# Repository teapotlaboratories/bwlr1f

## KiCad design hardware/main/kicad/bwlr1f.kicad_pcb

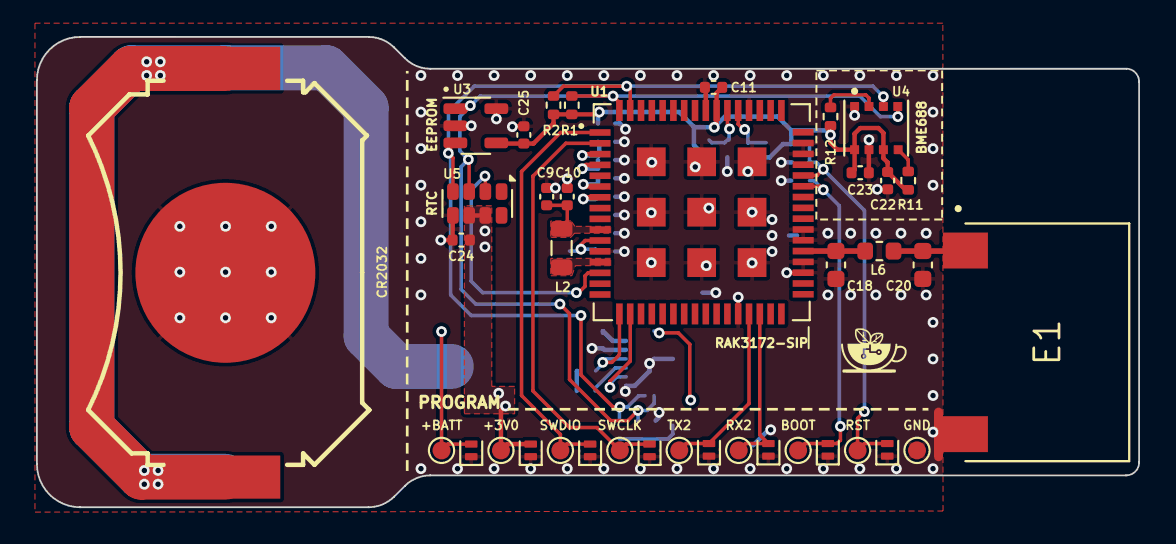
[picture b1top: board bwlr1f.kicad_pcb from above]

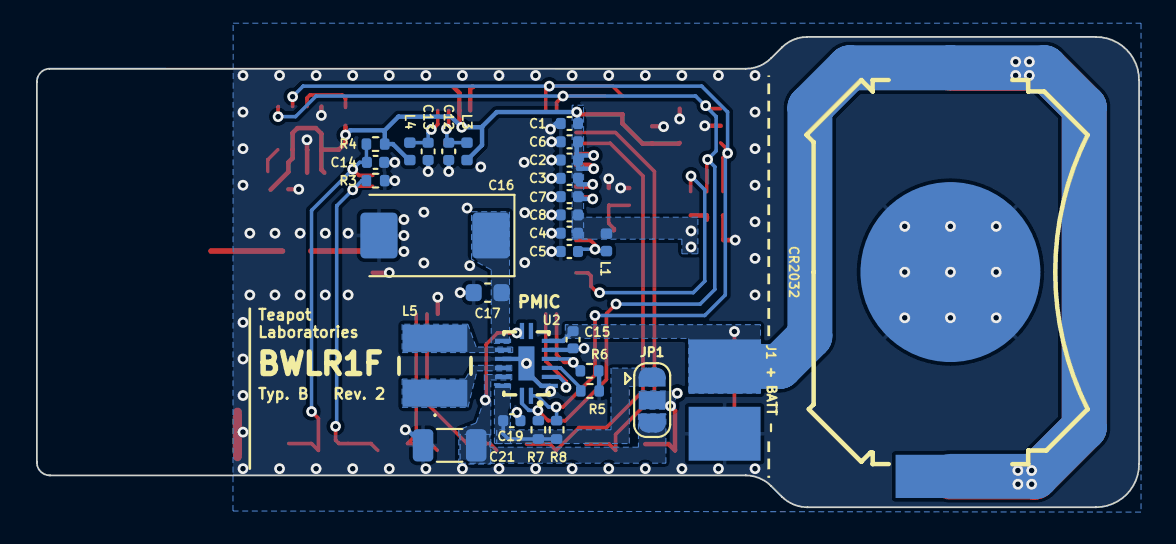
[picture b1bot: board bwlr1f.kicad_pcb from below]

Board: 4 copper layers, 61.2 x 26.1 mm, 68 parts (30 on the bottom side), 29 nets.

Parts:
BT1, BT2: Battery_Cell; BAT-SMD_MY-2032-12
C1, C3, C4: 4u7; C_0402_1005Metric
C2, C12, C13, C15, C19, C25: 1u; C_0402_1005Metric
C5, C6, C7, C8, C10, C11, C14, C22, C23, C24: 100n; C_0402_1005Metric
C9: 470n; C_0402_1005Metric
C16: 470u; CP_EIA-7343-40_Kemet-Y
C17: 10u; C_0603_1608Metric
C18, C20: DNP; C_0603_1608Metric
C21: 22u; C_1206_3216Metric
D1, D2, D3, D4, D5, D6, D7, D8: ESD5651N; D_SOD-882
E1: ANT-915-USP410; XDCR_ANT-915-USP410
J1: Conn_01x02; Battery_Pad
JP1: OUTPUT_SELECT; SolderJumper-3_P1.3mm_Open_RoundedPad1.0x1.5mm
L1, L3, L4: 120; L_0402_1005Metric
L2: 15u; L_0805_2012Metric
L5: 15u; 74404042150
L6: 0; L_0603_1608Metric
R1, R2: 4K7; R_0402_1005Metric
R3, R4, R11, R12: 10K; R_0402_1005Metric
R5, R6: 100K; R_0402_1005Metric
R7, R8: 1K; R_0402_1005Metric
TP1, TP2, TP3, TP4, TP5, TP6, TP7, TP8, TP9: ProgPin; TestPoint_Pad_D1.0mm
U1: RAK3172-SIP; RAK3172-SiP_LGA75
U2: NBM7100ABQX
U3: ZD24C08A; SOT-23-5
U4: BME688; BME680-PSON80P300X300X100-8N
U5: RV-3028-C7; MicroCrystal_C7_SON-8_1.5x3.2mm_P0.9mm

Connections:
+3V0: C1.2, C2.2, C3.2, C4.2, C6.2, C7.2, C8.2, C11.2, C22.2, C23.2, C24.2, C25.2, D8.2 (A2), JP1.2 (C), L1.1, L3.2, L4.2, R1.1, R2.1, R4.1, R11.1, R12.1, TP1.1, U1.3 (VDD), U1.4 (VBAT), U1.6 (VREF+), U1.7 (VDDA), U1.55 (VDD), U3.4 (VCC), U4.6 (VDDIO), U4.8 (VDD), U5.6 (VBACKUP), U5.7 (VDD)
/+VDP: C19.2, JP1.1 (A), R7.1, R8.1, U2.15 (VDP)
/ANT: C20.2, E1.1, L6.2
/BATT+: BT1.1 (+), BT2.1 (+), C15.2, D7.2 (A2), J1.1, TP2.1, U2.7 (VBT)
/BOOT: D1.2 (A2), R3.1, TP8.1, U1.43 (BOOT_0)
/RDY: U1.18 (PB7/UART1_RX), U2.3 (RDY)
/RF: C18.2, L6.1, U1.37 (RF_OUT)
/RST: C14.2, D2.2 (A2), R4.2, TP7.1, U1.44 (NRST)
/RTC_WKUP: U1.14 (PB3), U5.2 (~INT)
/RX2: D6.2 (A2), TP3.1, U1.30 (PA3/UART2_RX)
/SCL: R1.2, R7.2, U1.64 (PA12/I2C2_SCL), U2.16 (SCL), U3.1 (SCL), U4.4 (SCK), U5.3 (SCL)
/SDA: R2.2, R8.2, U1.63 (PA11/I2C2_SDA), U2.1 (SDA), U3.3 (SDA), U4.3 (SDI), U5.4 (SDA)
/START: R6.1, U1.17 (PB6/UART1_TX), U2.5 (START)
/SWCLK: D4.2 (A2), TP5.1, U1.2 (PA14/SWCLK)
/SWDIO: D3.2 (A2), TP6.1, U1.1 (PA13/SWDIO)
/TX2: D5.2 (A2), TP4.1, U1.29 (PA2/UART2_TX)
GND: BT1.2 (-), BT2.2 (-), C1.1, C2.1, C3.1, C4.1, C5.1, C6.1, C7.1, C8.1, C9.1, C10.1, C11.1, C12.1, C13.1, C14.1, C15.1, C16.2, C17.1, C18.1, C19.1, C20.1, C21.1, C22.1, C23.1, C24.1, C25.1, D1.1 (A1), D2.1 (A1), D3.1 (A1), D4.1 (A1), D5.1 (A1), D6.1 (A1), D7.1 (A1), D8.1 (A1), E1.2, J1.2, R3.2, R5.2, R6.2, TP9.1, U1.12 (GND), U1.28 (GND), U1.35 (GND), U1.36 (GND), U1.38 (GND), U1.39 (GND), U1.46 (GND), U1.47 (GND), U1.52 (GND), U1.56 (GND), U1.65 (GND), U1.66 (GND), U1.67 (GND), U1.68 (GND), U1.69 (GND), U1.70 (GND), U1.71 (GND), U1.72 (GND), U1.73 (GND), U2.2 (TST), U2.6 (VSS_1), U2.12 (VSSP), U2.17 (VSS_2), U3.2 (VSS), U3.5 (WP), U4.1 (GND), U4.7 (GND), U5.5 (VSS)
unnamed: C21.2, JP1.3 (B), U2.9 (VDHS), U2.14 (VDH)
unnamed: C5.2, L1.2, U1.11 (VDDMPS)
unnamed: C13.2, L4.1, U1.53 (VDDPA)
unnamed: C12.2, L3.1, U1.54 (VDDRF)
unnamed: C9.2, C10.2, L2.1, U1.10 (VFBSMPS)
unnamed: L2.2, U1.13 (VLXSMPS)
unnamed: R5.1, U2.4 (ADR)
unnamed: C16.1, C17.2, U2.10 (CAP)
unnamed: L5.1, U2.13 (LX1)
unnamed: L5.2, U2.11 (LX2)
unnamed: R12.2, U4.2 (CSB)
unnamed: R11.2, U4.5 (SDO)

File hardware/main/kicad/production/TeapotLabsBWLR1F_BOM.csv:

Id,Designator,Quantity,Manufacturer,Manufacturer Part Number,Value,Description,Footprint,Type,Distributor,Distributor Part Number,Distributor Link,Datasheet
1,"BT1,BT2",2,MYOUNG,MY-2032-12,Battery_Cell,Battery clip Nickel -25?~+85? Phosphor Bronze CR2032 SMD Button And Strip Battery Connector ROHS,bwlr1f:BAT-SMD_MY-2032-12,SMT,LCSC,C964833,https://www.lcsc.com/product-detail/Battery-Connectors_MYOUN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,https://datasheet.lcsc.com/lcsc/2012181809_MYOUNG-MY-2032-12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
2,"C1,C3,C4",3,Samsung Electro-Mechanics,CL05A475KP5NRNC,4u7,10V 4.7uF X5R ñ10% 0402 Multilayer Ceramic Capacitors MLCC - SMD/SMT ROHS,Capacitor_SMD:C_0402_1005Metric,SMT,LCSC,C368809,https://www.lcsc.com/product-detail/Multilayer-Ceramic-Capac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,https://datasheet.lcsc.com/lcsc/2304140030_Samsung-Electro-M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
3,"C2,C12,C13,C15,C19,C25",6,Samsung Electro-Mechanics,CL05A105KO5NNNC,1u,16V 1uF X5R ñ10% 0402 Multilayer Ceramic Capacitors MLCC - SMD/SMT ROHS ,Capacitor_SMD:C_0402_1005Metric,SMT,LCSC,C29266,https://www.lcsc.com/product-detail/Multilayer-Ceramic-Capac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,https://datasheet.lcsc.com/lcsc/2304140030_Samsung-Electro-M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
4,"C5,C6,C7,C8,C10,C11,C14,C22,C23,C24",10,Samsung Electro-Mechanics,CL05B104KO5NNNC,100n,16V 100nF X7R ñ10% 0402 Multilayer Ceramic Capacitors MLCC - SMD/SMT ROHS,Capacitor_SMD:C_0402_1005Metric,SMT,LCSC,C1525,https://www.lcsc.com/product-detail/Multilayer-Ceramic-Capac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,https://datasheet.lcsc.com/lcsc/2304140030_Samsung-Electro-M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
5,C9,1,Samsung Electro-Mechanics,CL05A474KP5NNNC,470n,10V 470nF X5R ñ10% 0402 Multilayer Ceramic Capacitors MLCC - SMD/SMT ROHS,Capacitor_SMD:C_0402_1005Metric,SMT,LCSC,C47339,https://www.lcsc.com/product-detail/Multilayer-Ceramic-Capac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,https://datasheet.lcsc.com/lcsc/2304140030_Samsung-Electro-M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
6,C16,1,KYOCERA AVX,TCJ5477M016R0100E,470u,Cap Tant Poly 470uF 16V 2917,Capacitor_Tantalum_SMD:CP_EIA-7343-40_Kemet-Y,SMT,Digikey,478-13191-1-ND,https://www.digikey.com/en/products/detail/kyocera-avx/TCJ54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,https://datasheets.kyocera-avx.com/TCJ.pdf
7,C17,1,Samsung Electro-Mechanics,CL10A106KO8NQNC,10u,16V 10uF X5R ñ10% 0603 Multilayer Ceramic Capacitors MLCC - SMD/SMT ROHS,Capacitor_SMD:C_0603_1608Metric,SMT,LCSC,C962136,https://www.lcsc.com/product-detail/Multilayer-Ceramic-Capac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,https://datasheet.lcsc.com/lcsc/2304140030_Samsung-Electro-M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
8,"C18,C20",2,-,-,DNP,DNP,Capacitor_SMD:C_0603_1608Metric,SMT,-,-,-,-
9,C21,1,Chinocera,HGC1206R7226K160NSPJ,22u,16V 22uF X7R ñ10% 1206 Multilayer Ceramic Capacitors MLCC - SMD/SMT ROHS,Capacitor_SMD:C_1206_3216Metric,SMT,LCSC,C7472972,https://www.lcsc.com/product-detail/Multilayer-Ceramic-Capac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,https://datasheet.lcsc.com/lcsc/2308041038_Chinocera-HGC1206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
10,"D1,D2,D3,D4,D5,D6,D7,D8",8,WILLSEMI(Will Semicon),ESD5651N-2/TR,ESD5651N,35A@8/20us 15V 4.5V DFN1006-2L Electrostatic and Surge Protection (TVS/ESD) ROHS,Diode_SMD:D_SOD-882,SMT,LCSC,C239784,https://www.lcsc.com/product-detail/Electrostatic-and-Surge-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,https://www.lcsc.com/datasheet/lcsc_datasheet_1808311544_WIL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
11,"L1,L3,L4",3,Murata Electronics,BLM15PD121SN1D,120,90mê ñ25% 120ê@100MHz 0402 Ferrite Beads ROHS,Inductor_SMD:L_0402_1005Metric,SMT,LCSC,C76891,https://www.lcsc.com/product-detail/Ferrite-Beads_Murata-Ele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,https://datasheet.lcsc.com/lcsc/2304140030_Murata-Electronic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
12,L2,1,TDK,MLZ2012M150WT000,15u,15uH ñ20% 120mA 950mê 0805 Inductors (SMD) ROHS,Inductor_SMD:L_0805_2012Metric,SMT,LCSC,C383402,https://www.lcsc.com/product-detail/Inductors-SMD_TDK-MLZ201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,https://datasheet.lcsc.com/lcsc/2304140030_TDK-MLZ2012M150WT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
13,L5,1,Wurth Elektronik,74404042150,15u,Fixed Ind 15uH 850mA 210 mOhm SMD,bwlr1f:74404042150,SMT,Digikey,732-5509-1-ND,https://www.digikey.com/en/products/detail/w%C3%BCrth-elektr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,https://www.we-online.com/katalog/datasheet/74404042150.pdf
14,L6,1,UNI-ROYAL(Uniroyal Elec),0603WAF0000T5E,0,100mW Thick Film Resistors 75V ñ1% 0ê 0603 Chip Resistor - Surface Mount ROHS ,Inductor_SMD:L_0603_1608Metric,SMT,LCSC,C21189,https://www.lcsc.com/product-detail/Chip-Resistor-Surface-Mo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,https://datasheet.lcsc.com/lcsc/2206010130_UNI-ROYAL-Uniroya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
15,"R1,R2",2,YAGEO,RC0402FR-074K7L,4K7,62.5mW Thick Film Resistors 50V ñ100ppm/? ñ1% 4.7kê 0402 Chip Resistor - Surface Mount ROHS,Resistor_SMD:R_0402_1005Metric,SMT,LCSC,C105871,https://www.lcsc.com/product-detail/Chip-Resistor-Surface-Mo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,https://datasheet.lcsc.com/lcsc/2304140030_YAGEO-RC0402FR-07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
16,"R3,R4,R11,R12",4,YAGEO,RC0402FR-0710KL,10K,62.5mW Thick Film Resistors 50V ñ100ppm/? ñ1% 10kê 0402 Chip Resistor - Surface Mount ROHS,Resistor_SMD:R_0402_1005Metric,SMT,LCSC,C60490,https://www.lcsc.com/product-detail/Chip-Resistor-Surface-Mo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,https://datasheet.lcsc.com/lcsc/2304140030_YAGEO-RC0402FR-07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
17,"R5,R6",2,YAGEO,RC0402FR-07100KL,100K,62.5mW Thick Film Resistors 50V ñ100ppm/? ñ1% 100kê 0402 Chip Resistor - Surface Mount ROHS ,Resistor_SMD:R_0402_1005Metric,SMT,LCSC,C60491,https://www.lcsc.com/product-detail/Chip-Resistor-Surface-Mo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,https://datasheet.lcsc.com/lcsc/2304140030_YAGEO-RC0402FR-07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
18,"R7,R8",2,YAGEO,RC0402FR-071KL,1K,62.5mW Thick Film Resistors 50V ñ100ppm/? ñ1% 1kê 0402 Chip Resistor - Surface Mount ROHS,Resistor_SMD:R_0402_1005Metric,SMT,LCSC,C106235,https://www.lcsc.com/product-detail/Chip-Resistor-Surface-Mo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,https://datasheet.lcsc.com/lcsc/2304140030_YAGEO-RC0402FR-07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
19,U1,1,RAKwireless,306039,RAK3172-SIP,RAK3172-SIP,bwlr1f:RAK3172-SiP_LGA75,SMT,RAKwireless,306039,Contact inquiry@rakwireless.com for SKU: 306039,https://docs.rakwireless.com/Product-Categories/WisDuo/RAK31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
20,U2,1,Nexperia,NBM7100ABQX,NBM7100ABQX,Coin Cell Battery Life Booster,bwlr1f:NBM7100ABQX,SMT,Digikey,1727-NBM7100ABQXCT-ND,https://www.digikey.com/en/products/detail/nexperia-usa-inc/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,https://assets.nexperia.com/documents/data-sheet/NBM7100.pdf
21,U3,1,Zetta,ZD24C08A-STGMT,ZD24C08A,8Kbit 1MHz I2C SOT-23-5 EEPROM ROHS,Package_TO_SOT_SMD:SOT-23-5,SMT,LCSC,C2896640,https://www.lcsc.com/product-detail/EEPROM_Zetta-ZD24C08A-ST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,https://datasheet.lcsc.com/lcsc/2109141830_Zetta-ZD24C08A-ST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
22,U4,1,Bosch Sensortec,BME688,BME688,Sensor Gas/Hum/Pres/Temp I2C SPI,bwlr1f:BME680-PSON80P300X300X100-8N,SMT,Digikey,828-BME688CT-ND,https://www.digikey.com/en/products/detail/bosch-sensortec/B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,https://www.bosch-sensortec.com/media/boschsensortec/downloa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
23,U5,1,Micro Crystal,RV-3028-C7 32.768kHz 1ppm TA QC ,RV-3028-C7,"Realtime Clock/Calendar I2C Interface, Extreme Low Power, 1.1 V to 5.5 V, MicroCrystal C7",Package_SON:MicroCrystal_C7_SON-8_1.5x3.2mm_P0.9mm,SMT,LCSC,C3019759,https://www.lcsc.com/product-detail/Real-Time-Clocks_Micro-C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,https://www.lcsc.com/datasheet/lcsc_datasheet_2302171010_Mic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

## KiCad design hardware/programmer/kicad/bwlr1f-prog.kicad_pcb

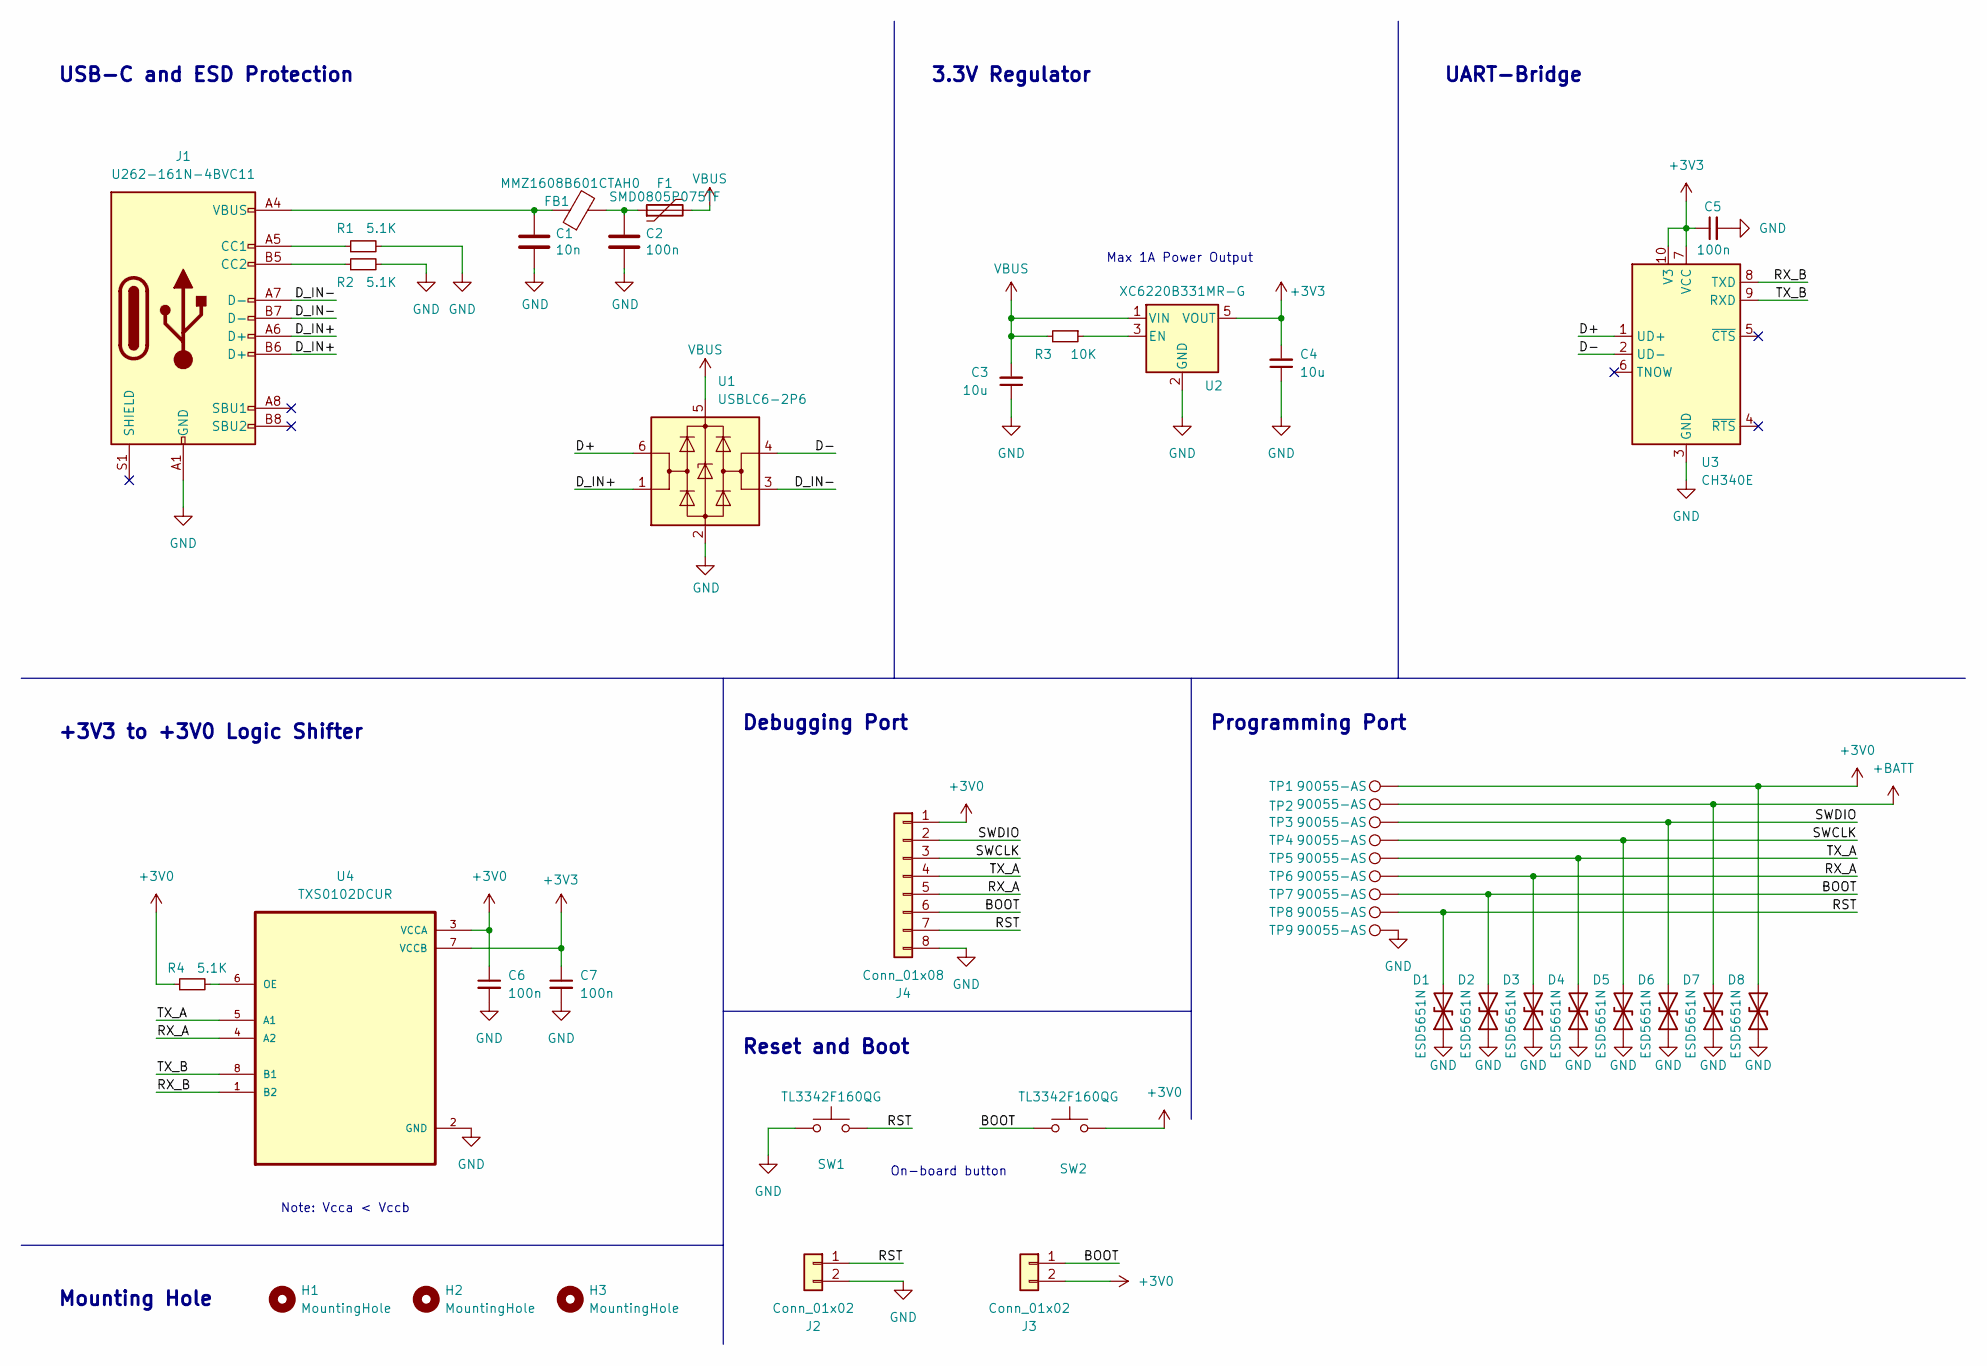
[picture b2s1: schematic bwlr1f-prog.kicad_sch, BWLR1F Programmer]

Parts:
C1: 10n; C_0402_1005Metric; Part Number CC0402KRX7R9BB103
C2: 100n; C_0402_1005Metric; Part Number CC0402KRX5R6BB104
C3, C4: 10u; C_0805_2012Metric; Part Description Ceramic Capacitor 10uF 10% 10V X5R
C5: 100n; C_0603_1608Metric; Part Description Ceramic Capacitor 100nF 10% 10V X7R
C6, C7: 100n; C_0402_1005Metric; Manufacturer Part Number CL05B104KO5NNNC
D1, D2, D3, D4, D5, D6, D7, D8: ESD5651N; D_SOD-882; Manufacturer Part Number ESD5651N-2/TR
F1: SMD0805P075TF; Fuse_0805_2012Metric; Part Number SMD0805P075TF
FB1: MMZ1608B601CTAH0; L_0603_1608Metric; Part Number MMZ1608B601CTAH0
H1, H2, H3: MountingHole; MountingHole_2.2mm_M2_DIN965_Pad
J1: U262-161N-4BVC11; USB_C_Receptacle_XKB_U262-16XN-4BVC11; Part Number U262-161N-4BVC11
J2, J3: Conn_01x02; PinHeader_1x02_P2.54mm_Horizontal
J4: Conn_01x08; PinHeader_1x08_P2.54mm_Horizontal
R1, R2, R4: 5.1K; R_0402_1005Metric; Part Description Resistor 5.1K 1% 62.5mW
R3: 10K; R_0603_1608Metric; Part Description Resistor 10k 5% 100mW
SW1, SW2: TL3342F160QG; SW_SPST_TL3342; Part Number TL3342F160QG
TP1, TP2, TP3, TP4, TP5, TP6, TP7, TP8, TP9: 90055-AS; Manufacturer Part Number 90055-AS
U1: USBLC6-2P6; SOT-666; Part Number USBLC6-2P6
U2: XC6220B331MR-G; SOT-23-5; Part Number XC6220B331MR-G
U3: CH340E; MSOP-10_3x3mm_P0.5mm; Part Number CH340E
U4: TXS0102DCUR; SOP50P310X90-8N; Manufacturer Part Number TXS0102DCUR

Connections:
+3V0: C6.1, D8.2 (A2), J3.2, J4.1, R4.1, SW2.2, TP1.1, U4.3 (VCCA)
+3V3: C4.2, C5.1, C7.1, U2.5 (VOUT), U3.7 (VCC), U3.10 (V3), U4.7 (VCCB)
+BATT: D7.2 (A2), TP2.1
/BOOT: D2.2 (A2), J3.1, J4.6, SW2.1, TP7.1
/D+: U1.6 (I/O1), U3.1 (UD+)
/D-: U1.4 (I/O2), U3.2 (UD-)
/D_IN+: J1.A6 (D+), J1.B6 (D+), U1.1 (I/O1)
/D_IN-: J1.A7 (D-), J1.B7 (D-), U1.3 (I/O2)
/RST: D1.2 (A2), J2.1, J4.7, SW1.2, TP8.1
/RX_A: D3.2 (A2), J4.5, TP6.1, U4.4 (A2)
/RX_B: U3.8 (TXD), U4.1 (B2)
/SWCLK: D5.2 (A2), J4.3, TP4.1
/SWDIO: D6.2 (A2), J4.2, TP3.1
/TX_A: D4.2 (A2), J4.4, TP5.1, U4.5 (A1)
/TX_B: U3.9 (RXD), U4.8 (B1)
GND: C1.2, C2.2, C3.1, C4.1, C5.2, C6.2, C7.2, D1.1 (A1), D2.1 (A1), D3.1 (A1), D4.1 (A1), D5.1 (A1), D6.1 (A1), D7.1 (A1), D8.1 (A1), J1.A1 (GND), J1.A12 (GND), J1.B1 (GND), J1.B12 (GND), J2.2, J4.8, R1.2, R2.2, SW1.1, TP9.1, U1.2 (GND), U2.2 (GND), U3.3 (GND), U4.2 (GND)
unnamed: C1.1, FB1.1, J1.A4 (VBUS), J1.A9 (VBUS), J1.B4 (VBUS), J1.B9 (VBUS)
unnamed: C2.1, F1.1, FB1.2
unnamed: J1.A5 (CC1), R1.1
unnamed: J1.B5 (CC2), R2.1
unnamed: R3.1, U2.3 (EN)
unnamed: R4.2, U4.6 (OE)
VBUS: C3.2, F1.2, R3.2, U1.5 (VBUS), U2.1 (VIN)

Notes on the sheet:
Debugging Port
Mounting Hole
UART-Bridge
Max 1A Power Output
Note: Vcca < Vccb
Programming Port
USB-C and ESD Protection
On-board button
Reset and Boot
+3V3 to +3V0 Logic Shifter
3.3V Regulator

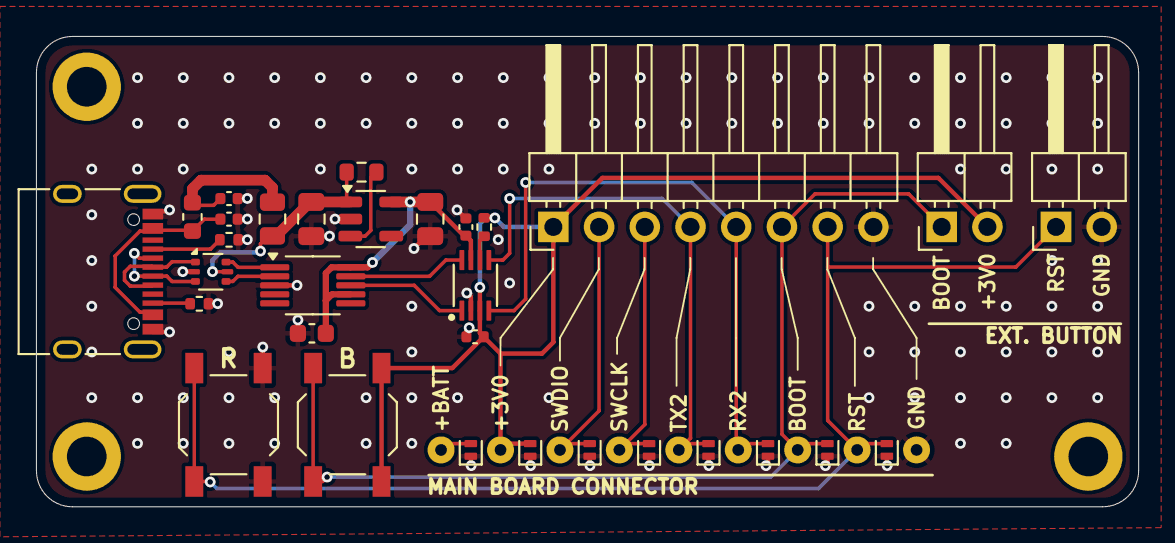
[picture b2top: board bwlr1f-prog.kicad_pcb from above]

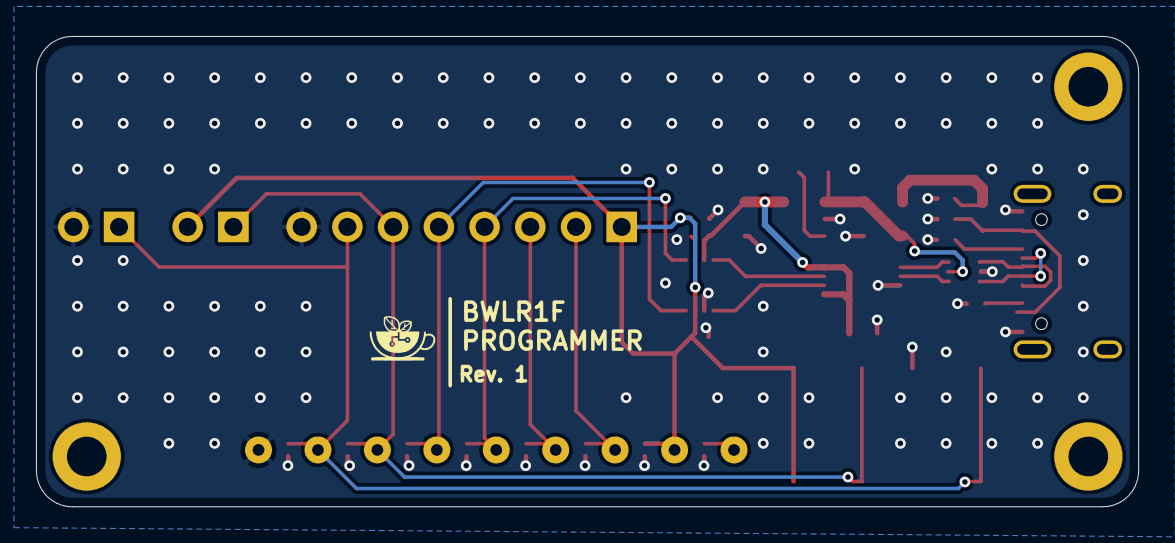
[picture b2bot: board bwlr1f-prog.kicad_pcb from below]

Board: 2 copper layers, 61.2 x 26.1 mm, 43 parts (9 on the bottom side), 23 nets.

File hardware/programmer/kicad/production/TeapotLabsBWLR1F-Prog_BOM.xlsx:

Id | Designator | Quantity | Manufacturer | Manufacturer Part Number | Value | Description | Footprint | Type | Distributor | Distributor Part Number | Distributor Link | Datasheet
1 | C1 | 1 | YAGEO | CC0402KRX7R9BB103 | 10n | 50V 10nF X7R ±10% 0402 Multilayer Ceramic Capacitors MLCC - SMD/SMT ROHS | Capacitor_SMD:C_0402_1005Metric | SMT | LCSC | C60133 | https://www.lcsc.com/product-detail/Multilayer-Ceramic-Capac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 | https://www.lcsc.com/datasheet/lcsc_datasheet_2304140030_YAG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
2 | C2,C6,C7 | 3 | Samsung Electro-Mechanics | CL05B104KO5NNNC | 100n | 16V 100nF X7R ±10% 0402 Multilayer Ceramic Capacitors MLCC - SMD/SMT ROHS | Capacitor_SMD:C_0402_1005Metric | SMT | LCSC | C1525 | https://www.lcsc.com/product-detail/Multilayer-Ceramic-Capac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 | https://www.lcsc.com/datasheet/lcsc_datasheet_2304140030_Sam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
3 | C3,C4 | 2 | Samsung Electro-Mechanics | CL21A106KPFNNNE | 10u | 10V 10uF X5R ±10% 0805 Multilayer Ceramic Capacitors MLCC - SMD/SMT ROHS | Capacitor_SMD:C_0805_2012Metric | SMT | LCSC | C17024 | https://www.lcsc.com/product-detail/Multilayer-Ceramic-Capac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 | https://www.lcsc.com/datasheet/lcsc_datasheet_2304140030_Sam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
4 | C5 | 1 | Samsung Electro-Mechanics | CL10B104KB8NNNC | 100n | 50V 100nF X7R ±10% 0603 Multilayer Ceramic Capacitors MLCC - SMD/SMT ROHS | Capacitor_SMD:C_0603_1608Metric | SMT | LCSC | C1591 | https://www.lcsc.com/product-detail/Multilayer-Ceramic-Capac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 | https://www.lcsc.com/datasheet/lcsc_datasheet_2304140030_Sam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
5 | D1,D2,D3,D4,D5,D6,D7,D8 | 8 | WILLSEMI(Will Semicon) | ESD5651N-2/TR | ESD5651N | 35A@8/20us 15V 4.5V DFN1006-2L Electrostatic and Surge Protection (TVS/ESD) ROHS | Diode_SMD:D_SOD-882 | SMT | LCSC | C239784 | https://www.lcsc.com/product-detail/Electrostatic-and-Surge-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 | https://www.lcsc.com/datasheet/lcsc_datasheet_1808311544_WIL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
6 | F1 | 1 | RUILON(Shenzhen Ruilongyuan Elec) | SMD0805P075TF | SMD0805P075TF | 6V 750mA 40A 1.5A 0805 Resettable Fuses ROHS | Fuse:Fuse_0805_2012Metric | SMT | LCSC | C20979 | https://www.lcsc.com/product-detail/Resettable-Fuses_RUILON-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 | https://www.lcsc.com/datasheet/lcsc_datasheet_2403081022_RUI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
7 | FB1 | 1 | TDK | MMZ1608B601CTAH0 | MMZ1608B601CTAH0 | 400m? ±25% 600?@100MHz 0603 Ferrite Beads ROHS | Inductor_SMD:L_0603_1608Metric | SMT | LCSC | C97120 | https://www.lcsc.com/product-detail/Ferrite-Beads_TDK-MMZ160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 | https://www.lcsc.com/datasheet/lcsc_datasheet_2304140030_TDK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
8 | J1 | 1 | XKB Connectivity | U262-161N-4BVC11 | U262-161N-4BVC11 | 3A USB 3.1 1 260? Horizontal attachment 16P Female -40?~+85? Gold Copper Alloy 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 | bwlr1f-prog:USB_C_Receptacle_XKB_U262-16XN-4BVC11 | SMT | LCSC | C319148 | https://www.lcsc.com/product-detail/USB-Connectors_XKB-Conne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 | https://www.lcsc.com/datasheet/lcsc_datasheet_2405311753_XKB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
9 | J2,J3 | 2 | - | - | Conn_01x02 | DNP | Connector_PinHeader_2.54mm:PinHeader_1x02_P2.54mm_Horizontal | THT | - | - | - | -
10 | J4 | 1 | - | - | Conn_01x08 | DNP | Connector_PinHeader_2.54mm:PinHeader_1x08_P2.54mm_Horizontal | THT | - | - | - | -
11 | R1,R2,R4 | 3 | UNI-ROYAL(Uniroyal Elec) | 0402WGF5101TCE | 5.1K | 62.5mW Thick Film Resistors 50V ±100ppm/? ±1% 5.1k? 0402 Chip Resistor - Surfac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 | Resistor_SMD:R_0402_1005Metric | SMT | LCSC | C25905 | https://www.lcsc.com/product-detail/Chip-Resistor-Surface-Mo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 | https://www.lcsc.com/datasheet/lcsc_datasheet_2206010045_UNI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
12 | R3 | 1 | UNI-ROYAL(Uniroyal Elec) | 0603WAF1002T5E | 10K | 100mW Thick Film Resistors 75V ±100ppm/? ±1% 10k? 0603 Chip Resistor - Surface 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 | Resistor_SMD:R_0603_1608Metric | SMT | LCSC | C25804 | https://www.lcsc.com/product-detail/Chip-span-style-backgrou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 | https://www.lcsc.com/datasheet/lcsc_datasheet_2206010045_UNI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
13 | SW1,SW2 | 2 | E-Switch | TL3342F160QG | TL3342F160QG | SPST SMD NO 50mA 100M? 100000 Times 12V 160gf@±50gf | Button_Switch_SMD:SW_SPST_TL3342 | SMT | LCSC | C2886898 | https://www.lcsc.com/product-detail/Tactile-Switches_E-Switc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 | https://www.lcsc.com/datasheet/lcsc_datasheet_2109061530_E-S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
14 | TP1,TP2,TP3,TP4,TP5,TP6,TP7,TP8,TP9 | 9 | Preci-Dip | 90055-AS | 90055-AS | Contact Spring Loaded SMD Gold | bwlr1f-prog:90055-AS | THT | Digikey | 1212-1855-ND | https://www.digikey.com/en/products/detail/preci-dip/90055-A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 | https://mm.digikey.com/Volume0/opasdata/d220001/medias/docus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
15 | U1 | 1 | STMicroelectronics | USBLC6-2P6 | USBLC6-2P6 | 5A 17V 6V Unidirectional 5.25V SOT-666-6 ESD and Surge Protection (TVS/ESD) ROHS | Package_TO_SOT_SMD:SOT-666 | SMT | LCSC | C15999 | https://www.lcsc.com/product-detail/ESD-Protection-Devices_S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 | https://www.lcsc.com/datasheet/lcsc_datasheet_1809192323_STM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
16 | U2 | 1 | Torex Semiconductor | XC6220B331MR-G | XC6220B331MR-G | 50dB@(1kHz) 1A Fixed 3.3V Positive electrode 6V SOT-25-5 Voltage Regulators - L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 | Package_TO_SOT_SMD:SOT-23-5 | SMT | LCSC | C86534 | https://www.lcsc.com/product-detail/Linear-Voltage-Regulator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 | https://www.lcsc.com/datasheet/lcsc_datasheet_1810010324_Tor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
17 | U3 | 1 | WCH | CH340E | CH340E | 2Mbps Transceiver USB 2.0 MSOP-10 USB Converters ROHS | Package_SO:MSOP-10_3x3mm_P0.5mm | SMT | LCSC | C99652 | https://www.lcsc.com/product-detail/USB-ICs_WCH-Jiangsu-Qin-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 | https://www.lcsc.com/datasheet/lcsc_datasheet_2403131141_WCH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
18 | U4 | 1 | Texas Instruments | TXS0102DCUR | TXS0102DCUR | 2.3V~5.5V 1 2 1.65V~3.6V 24Mbps VSSOP-8 Translators, Level Shifters ROHS | bwlr1f-prog:SOP50P310X90-8N | SMT | LCSC | C53434 | https://www.lcsc.com/product-detail/Translators-Level-Shifte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 | https://www.lcsc.com/datasheet/lcsc_datasheet_1810292010_Tex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

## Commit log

2023-12-02 initial file
2023-12-16 finishing
2023-12-16 add notes
2023-12-16 generate bom & cpl
2023-12-23 finish bom & cpl
2024-01-08 add mosfet switch for M_DRV
2024-01-08 wip: re-route layout
2024-01-09 wip: re-layout
2024-01-09 wip: initial pcb prod
2024-01-09 add battery cr2302 holder
2024-01-09 add battery pack
2024-01-10 first production file revision 1
2024-01-10 clean-up
2024-01-10 remove break away tabs
2024-01-10 fix In2 ground
2024-01-11 fix wrong qty for Q1 and Q1
2024-01-26 change antenna
2024-01-26 update layout
2024-01-30 Revert "update layout"
    This reverts commit 7d4c2235c3ae4d9f911583b993bcb32887b0ae1e.
2024-01-30 Revert "change antenna"
    This reverts commit 46c20b2a2dd1e0a5efdce99ceacd3ab7d772dc0d.
2024-01-30 add initial mdrv latcher circuit
2024-07-31 bwlr1f update
2024-08-03 Add programmer file
2024-08-05 Update Programmer
2024-08-06 Added ESD to main board
2024-08-06 Update PCB layout
2024-08-12 Update for Programmer
2024-08-13 Finish Production File for Main Board
2024-08-13 Finish Production File for Programmer Board
2024-08-13 Update for Main Board
2024-08-22 Change PCB Antenna
2024-08-22 Main Board Revision
2024-08-22 Revert "Main Board Revision"
    This reverts commit c5b913284f91f81721d22b196ba55e4d9f276ba3.
2024-08-26 Revision finish, update production file
2024-08-28 Revert "Change PCB Antenna"
    This reverts commit 5ca8b7b7452485b6d3384e8d9324ab527cbc9679.
2024-08-28 update silkscreen rev identifier
2024-08-28 update sheets info
2024-08-28 update production files
